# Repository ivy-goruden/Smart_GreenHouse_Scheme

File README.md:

# Teplica_Scheme

Это плата для проекта [teplica2](https://github.com/ivy-goruden/teplica2). Проект представляет собой систему автоматизации для теплицы, управляемую микроконтроллером Arduino Nano.

Разработана в KiCad.

## Структура проекта

* `/Teplica`: Содержит файлы проекта KiCad (схема и печатная плата).
* `/components`: Библиотека символов компонентов для KiCad.
* `Teplica.svg`: Изображение схемы.
* `board.png`: 3D-вид печатной платы.

## Компоненты

Схема включает в себя следующие основные компоненты:

* **Микроконтроллер:** Arduino Nano
* **Часы реального времени:** DS1307
* **Датчики:**
  * Датчик влажности воздуха (HumS1)
  * 3 датчика влажности почвы (MoistS1, MoistS2, MoistS3)
  * Поплавковый датчик уровня жидкости (Bobber1)
* **Исполнительные устройства:**
  * 3 насоса (Pump 1, Pump 2, Pump 3)
  * Освещение (Lamp)
* **Интерфейс пользователя:**
  * LCD-дисплей

## Схема

## Внешний вид платы

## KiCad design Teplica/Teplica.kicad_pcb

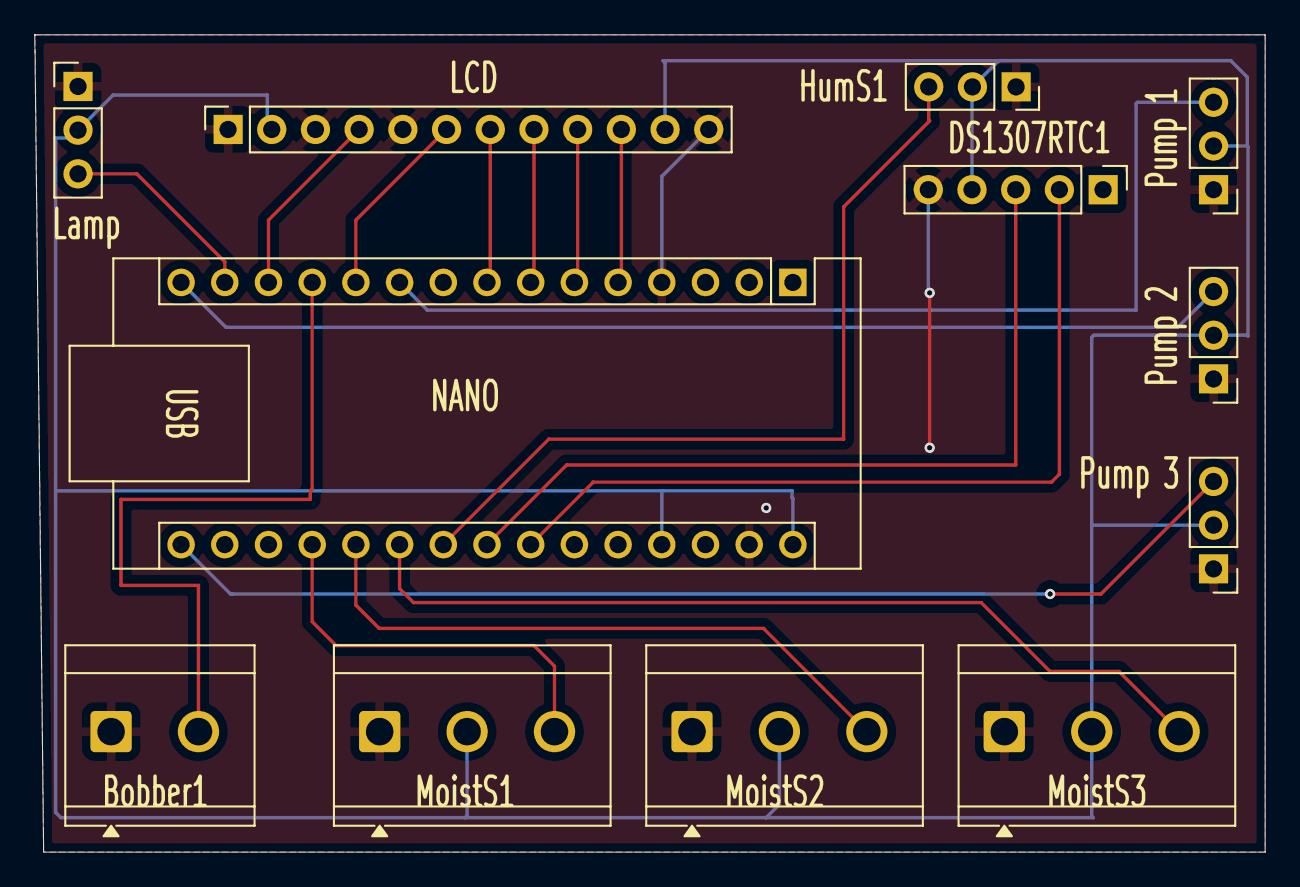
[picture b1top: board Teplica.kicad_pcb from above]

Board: 2 copper layers, 71.5 x 47.5 mm, 12 parts (0 on the bottom side), 19 nets.

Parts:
Bobber1: TerminalBlock_CUI_TB007-508-02_1x02_P5.08mm_Horizontal
DS1307RTC1: PinHeader_1x05_P2.54mm_Vertical
HumS1: PinSocket_1x03_P2.54mm_Vertical
LCD: PinSocket_1x12_P2.54mm_Vertical
Lamp: PinHeader_1x03_P2.54mm_Vertical
MoistS1, MoistS2, MoistS3: TerminalBlock_CUI_TB007-508-03_1x03_P5.08mm_Horizontal
NANO: Arduino_Nano
Pump 1, Pump 2, Pump 3: PinHeader_1x03_P2.54mm_Vertical

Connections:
+5V: DS1307RTC1.4 (VCC), HumS1.2 (VCC), LCD.2 (VCC), LCD.11 (+LED), Lamp.2 (VCC), MoistS1.2 (VCC), MoistS2.2 (VCC), MoistS3.2 (VCC), NANO.27 (5V), NANO.30 (VIN), Pump 1.2 (VCC), Pump 2.2 (VCC), Pump 3.2 (VCC)
/BobberS: Bobber1.2 (SIGNAL), NANO.12 (D9)
/HumS: HumS1.3 (SIGNAL), NANO.22 (A3)
/LAMP_S: Lamp.3 (S), NANO.14 (D11)
/LCD2: LCD.4 (A0), NANO.13 (D10)
/LCD4: LCD.6 (E), NANO.11 (D8)
/LCD5: LCD.7 (DB4), NANO.8 (D5)
/LCD6: LCD.8 (DB5), NANO.7 (D4)
/LCD7: LCD.9 (DB6), NANO.6 (D3)
/LCD8: LCD.10 (DB7), NANO.5 (D2)
/MoistureS1: MoistS3.3 (SIGNAL), NANO.21 (A2)
/MoistureS2: MoistS2.3 (SIGNAL), NANO.20 (A1)
/MoistureS3: MoistS1.3 (SIGNAL), NANO.19 (A0)
/PUMP_S1: NANO.10 (D7), Pump 1.3 (S)
/PUMP_S2: NANO.15 (D12), Pump 2.3 (S)
/PUMP_S3: NANO.16 (D13), Pump 3.3 (S)
/SCL: DS1307RTC1.2 (SCL), NANO.24 (A5)
/SDA: DS1307RTC1.3 (SDA), NANO.23 (A4)
GND: Bobber1.1 (GND), DS1307RTC1.5 (GND), HumS1.1 (GND), LCD.1 (GND), LCD.3 (U0), LCD.5 (R/W), LCD.12 (-LED), Lamp.1 (GND), MoistS1.1 (GND), MoistS2.1 (GND), MoistS3.1 (GND), NANO.4 (GND), NANO.29 (GND), Pump 1.1 (GND), Pump 2.1 (GND), Pump 3.1 (GND)

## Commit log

2026-03-14 init commit
2026-03-22 Recover project files
2026-03-23 finished board
